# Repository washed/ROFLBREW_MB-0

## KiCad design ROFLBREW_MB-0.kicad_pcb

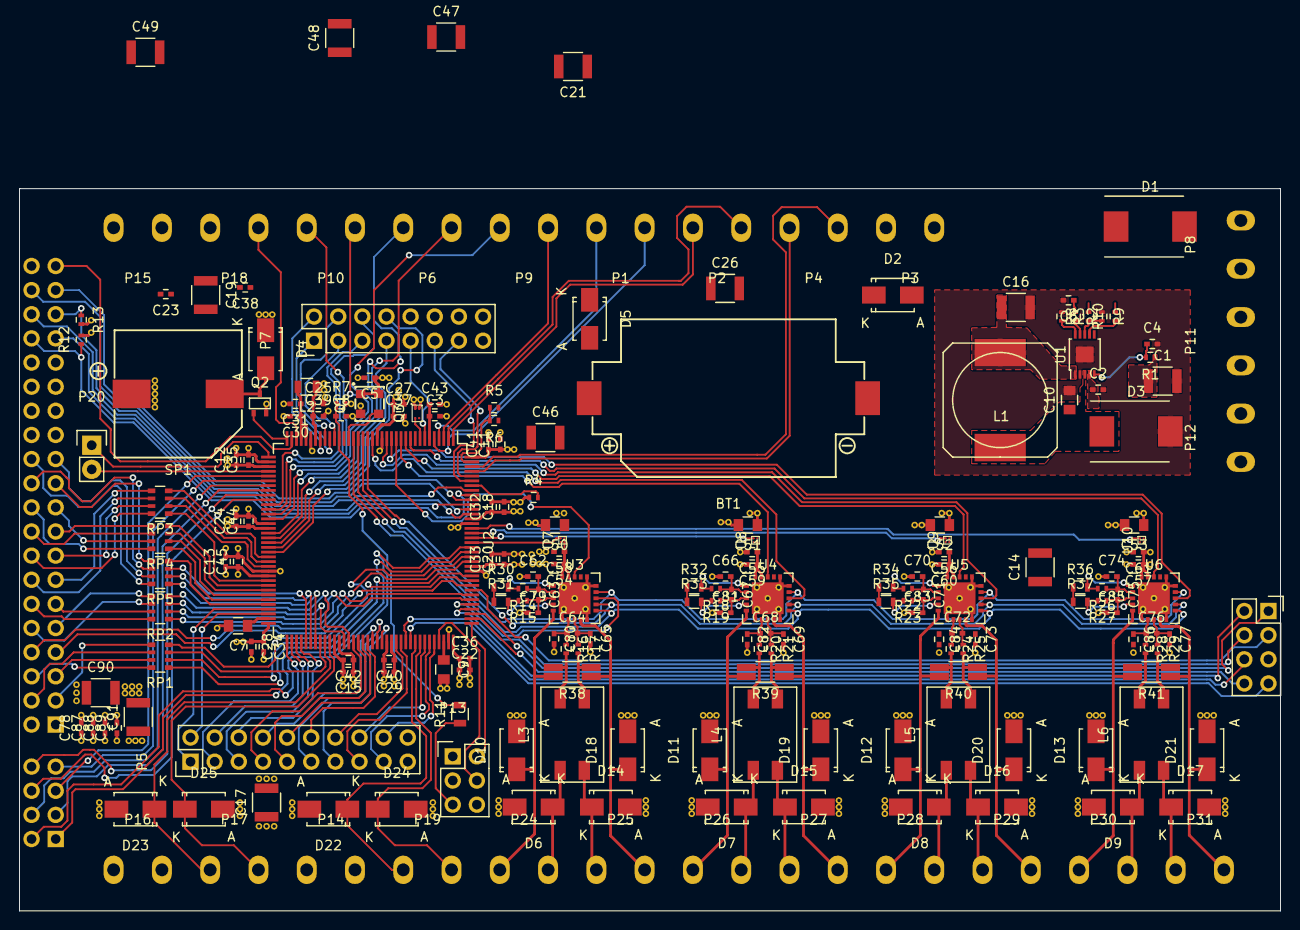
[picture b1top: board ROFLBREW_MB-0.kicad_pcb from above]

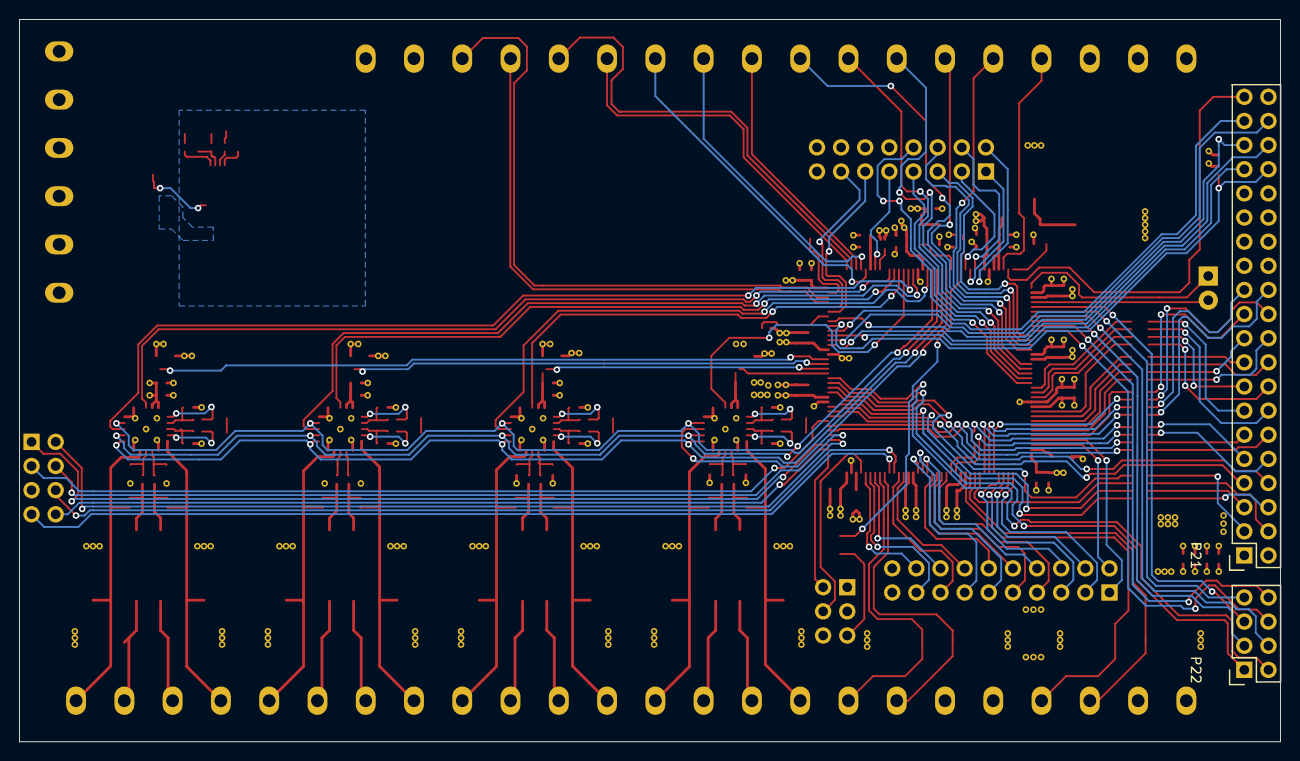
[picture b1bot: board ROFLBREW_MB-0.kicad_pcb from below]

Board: 4 copper layers, 132.7 x 76.0 mm, 214 parts (2 on the bottom side), 202 nets.

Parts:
BT1: Battery; MPDBA2032SM
C1, C14, C16, C17, C19, C21, C26, C46, C47, C48, C49, C90, C91: 22µ; C_1210
C2, C3, C4, C5, C6, C8, C11, C12, C13, C15, C18, C20, C22, C23, C24, C25, C27, C28, C29, C31, C43, C54, C55, C56, C57, C58, C59, C60, C61, C88, C89: 100n; C_0402
C7, C9: 2µ2; C_0805
C10: 470n; C_0805
C30, C32, C33, C34, C35, C36, C37, C38, C39, C40, C41, C42, C44, C45, C63, C64, C67, C68, C71, C72, C75, C76, C78, C87: 10n; C_0402
C50, C51, C52, C53: 1µ; C_0805
C62, C65, C66, C69, C70, C73, C74, C77, C79, C80, C81, C82, C83, C84, C85, C86: 1n; C_0402
D1, D3: MBRS340; DO-214AB
D2, D4, D5: B240; SMA_Standard
D6, D7, D8, D9, D10, D11, D12, D13, D14, D15, D16, D17, D18, D19, D20, D21, D22, D23, D24, D25: TVS; SMA_Standard
L1: 4µ7; SELF-WE-PD-XXL
L2: Ferrite Bead; R_0805
L3, L4, L5, L6: WE-SL2
P1, P2, P3, P4, P6, P8, P9, P10, P11, P12, P14, P15, P16, P17, P18, P19, P24, P25, P26, P27, P28, P29, P30, P31: CONN_01X02; PM_5.08_2
P5: CONN_02X10; Pin_Header_Straight_2x10
P7: CONN_02X08; Pin_Header_Straight_2x08
P13: CONN_02X03; Pin_Header_Straight_2x03
P20: CONN_01X02; Pin_Header_Straight_1x02
P21: CONN_02X20; Socket_Strip_Straight_2x20
P22, P23: CONN_02X04; Socket_Strip_Straight_2x04
Q1: ASEM1
Q2: MUN5233T1G; SC-70
Q3: ASTMTXK
R1, R9, R10: 100K; R_0402
R2: 14K; R_0402
R3: 40K2; R_0402
R4, R5, R6, R7: 10K; R_0402
R8: 316K; R_0402
R11: 0R; R_0805
R12, R13: 4K7 DNI; R_0402
R14, R15, R16, R17, R18, R19, R20, R21, R22, R23, R24, R25, R26, R27, R28, R29: TBD R; R_0402
R30, R31, R32, R33, R34, R35, R36, R37: 2k 0.01%; R_0603
R38, R39, R40, R41: 1k RTD PT1000 DNI; R_1206_RTD_SPLITPADS
RP1, RP2, RP3, RP4, RP5: R_PACK4; R_Array_Convex_4x0603
SP1: SPEAKER; CT-1205H
U1: LT3480; MSOP-10-1EP_3x3mm_Pitch0.5mm
U2: STM32F756ZGTx; LQFP-144_20x20mm_Pitch0.5mm
U3, U4, U5, U6: MAX31865; QFN-20-1EP_5x5mm_Pitch0.65mm
U7, U8, U9, U10: TPS2290x; TPS229x

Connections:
+3V3: C5.1, C11.1, C12.1, C13.1, C14.1, C15.1, C16.1, C17.1, C18.1, C19.1, C20.1, C21.1, C22.1, C23.1, C24.1, C25.1, C27.1, C28.1, C29.1, C32.1, C33.1, C34.1, C35.1, C36.1, C37.1, C38.1, C39.1, C40.1, C41.1, C42.1, C44.1, C45.1, C46.1, C47.1, C48.1, C49.1, C50.1, C51.1, C52.1, C53.1, C78.1, C87.1, C88.1, C89.1, C90.1, C91.1, D4.1, L1.2, L2.1, P3.1, P12.2, P13.1, P14.1, P15.1, P16.1, P21.2, Q1.1, Q1.4, R5.2, R7.2, R8.2, R10.2, R12.2, R13.2, SP1.1, U1.1, U2.17, U2.30, U2.39, U2.52, U2.62, U2.72, U2.84, U2.95, U2.108, U2.121, U2.131, U2.144, U7.A1, U8.A1, U9.A1, U10.A1
+12V: C1.1, C2.1, D1.1, R1.1, U1.4
+BATT: C3.1, C26.1, C43.1, D2.1, D5.1, Q3.3, U2.6
/ADC1_IN0: P18.1, U2.34
/ADC1_IN4: P20.2, U2.40
/ADC1_IN9: P7.5, U2.47
/ADC1_IN10: P7.3, U2.26
/ADC1_IN11: P7.1, U2.27
/ADC1_IN12: P7.4, U2.28
/ADC1_IN13: P7.2, U2.29
/FLASH_CS: P22.8, U2.45
/FLASH_WP: P22.6, U2.46
/FONT/FLASH_MISO: P22.7, U2.42
/FONT/FLASH_MOSI: P22.4, U2.43
/FONT/FLASH_SCK: P22.5, U2.41
/FONT_CS: P22.3, U2.44
/LCD_BLT: P21.39, U2.35
/LCD_CS: P21.3, RP1.5
/LCD_CS_MCU: RP1.4, U2.123
/LCD_D0: P21.9, RP2.5
/LCD_D0_MCU: RP2.3, U2.85
/LCD_D1: P21.10, RP2.6
/LCD_D1_MCU: RP2.4, U2.86
/LCD_D2: P21.11, RP2.7
/LCD_D2_MCU: RP2.2, U2.114
/LCD_D3: P21.12, RP2.8
/LCD_D3_MCU: RP2.1, U2.115
/LCD_D4: P21.13, RP3.5
/LCD_D4_MCU: RP3.4, U2.58
/LCD_D5: P21.14, RP3.6
/LCD_D5_MCU: RP3.3, U2.59
/LCD_D6: P21.15, RP3.7
/LCD_D6_MCU: RP3.2, U2.60
/LCD_D7: P21.16, RP3.8
/LCD_D7_MCU: RP3.1, U2.63
/LCD_D8: P21.17, RP4.5
/LCD_D8_MCU: RP4.4, U2.64
/LCD_D9: P21.18, RP4.6
/LCD_D9_MCU: RP4.3, U2.65
/LCD_D10: P21.19, RP4.7
/LCD_D10_MCU: RP4.2, U2.66
/LCD_D11: P21.20, RP4.8
/LCD_D11_MCU: RP4.1, U2.67
/LCD_D12: P21.21, RP5.5
/LCD_D12_MCU: RP5.4, U2.68
/LCD_D13: P21.22, RP5.6
/LCD_D13_MCU: RP5.3, U2.77
/LCD_D14: P21.23, RP5.7
/LCD_D14_MCU: RP5.2, U2.78
/LCD_D15: P21.24, RP5.8
/LCD_D15_MCU: RP5.1, U2.79
/LCD_DATA/CMD: P21.4, RP1.6
/LCD_DATA/CMD_MCU: RP1.3, U2.80
/LCD_GPIO1: P22.1, U2.124
/LCD_GPIO2: P22.2, U2.125
/LCD_RD#: P21.5, RP1.7
/LCD_RD#_MCU: RP1.2, U2.118
/LCD_TE: P21.8, U2.122
/LCD_WR#: P21.6, RP1.8
/LCD_WR#_MCU: RP1.1, U2.119
/LCD_nRST: P21.7, U2.117
/PA10: P5.16, U2.102
/PA11: P5.17, U2.103
/PA12: P5.18, U2.104
/PB2: P7.6, U2.48
/PB8: P7.11, U2.139
/PB9: P7.13, U2.140
/PB10: P5.1, U2.69
/PB11: P5.2, U2.70
/PB12: P5.3, U2.73
/PB13: P5.4, U2.74
/PB14: P5.5, U2.75
/PB15: P5.6, U2.76
/PC13: P7.9, U2.7
/PG0: P7.7, U2.56
/PG1: P7.8, U2.57
/PG2: P5.7, U2.87
/PG3: P5.9, U2.88
/PG4: P5.10, U2.89
/PG5: P5.12, U2.90
/PG6: P5.8, U2.91
/PG7: P5.11, U2.92
/PG8: P5.13, U2.93
/PWM_1: Q2.1, U2.36
/PWM_2: P20.1, U2.37
/ROTENC0_A: D22.1, P19.1, U2.100
/ROTENC0_B: D24.1, P19.2, U2.101
/ROTENC1_A: D23.1, P17.1, U2.81
/ROTENC1_B: D25.1, P17.2, U2.82
/RTC_OSC: Q3.2, U2.8
/RTD0_CS: U2.22, U3.13
/RTD0_DRDY: U2.13, U3.18
/RTD1_CS: U2.18, U4.13
/RTD1_DRDY: U2.12, U4.18
/RTD2_CS: U2.15, U5.13
/RTD2_DRDY: U2.11, U5.18
/RTD3_CS: U2.14, U6.13
/RTD3_DRDY: U2.10, U6.18
/RTD_MISO: U2.20, U3.14, U4.14, U5.14, U6.14
/RTD_MOSI: U2.21, U3.11, U4.11, U5.11, U6.11
/RTD_PWR_0: U2.126, U7.B1
/RTD_PWR_1: U2.127, U8.B1
/RTD_PWR_2: U2.128, U9.B1
/RTD_PWR_3: U2.129, U10.B1
/RTD_SCK: U2.19, U3.12, U4.12, U5.12, U6.12
/SD_CARDD: P23.8, U2.110
/SD_CLK: P23.4, U2.113
/SD_CMD: P23.3, U2.116
/SD_D0: P23.6, U2.98
/SD_D1: P23.7, U2.99
/SD_D2: P23.1, U2.111
/SD_D3: P23.2, U2.112
/SPI4_CS0: P2.1, U2.2
/SPI4_CS1: P9.1, U2.3
/SPI4_MISO: P1.2, U2.4
/SPI4_MOSI: P1.1, U2.5
/SPI4_SCK: P2.2, U2.1
/SYS_JTCK: P13.2, U2.109
/SYS_JTMS: P13.4, U2.105
/TIM3_CH1: P5.14, U2.96
/TIM3_CH2: P5.15, U2.97
/TP_INT: P21.36, U2.132
/TP_PEN: P21.38, U2.133
/TP_SCL: P21.34, R12.1, U2.136
/TP_SDA: P21.35, R13.1, U2.137
/TP_WAKE: P21.37, U2.135
/TP_nRST: P21.33, U2.134
/UART8_RX: P4.2, U2.141
/UART8_TX: P4.1, U2.142
/nRST: C8.1, R7.1, R11.2, U2.25
GND: BT1.2, C1.2, C2.2, C3.2, C4.2, C5.2, C6.2, C7.2, C8.2, C9.2, C10.2, C11.2, C12.2, C13.2, C14.2, C15.2, C16.2, C17.2, C18.2, C19.2, C20.2, C21.2, C22.2, C23.2, C24.2, C25.2, C26.2, C27.2, C28.2, C29.2, C30.2, C31.2, C32.2, C33.2, C34.2, C35.2, C36.2, C37.2, C38.2, C39.2, C40.2, C41.2, C42.2, C43.2, C44.2, C45.2, C46.2, C47.2, C48.2, C49.2, C50.2, C51.2, C52.2, C53.2, C54.2, C55.2, C56.2, C57.2, C58.2, C59.2, C60.2, C61.2, C62.1, C65.2, C66.1, C69.2, C70.1, C73.2, C74.1, C77.2, C78.2, C79.1, C80.2, C81.1, C82.2, C83.1, C84.2, C85.1, C86.2, C87.2, C88.2, C89.2, C90.2, C91.2, D3.2, D6.2, D7.2, D8.2, D9.2, D10.2, D11.2, D12.2, D13.2, D14.2, D15.2, D16.2, D17.2, D18.2, D19.2, D20.2, D21.2, D22.2, D23.2, D24.2, D25.2, P3.2, P8.1, P11.1, P12.1, P13.3, P14.2, P15.2, P16.2, P21.1, P21.40, P23.5, Q1.2, Q2.2, Q3.1, Q3.4, R3.1, R4.1, R6.1, R9.1, U1.2, U1.11, U2.16, U2.31, U2.38, U2.51, U2.61, U2.83, U2.94, U2.107, U2.120, U2.130, U3.6, U3.10, U3.15, U3.16, U3.21, U4.6, U4.10, U4.15, U4.16, U4.21, U5.6, U5.10, U5.15, U5.16, U5.21, U6.6, U6.10, U6.15, U6.16, U6.21, U7.B2, U8.B2, U9.B2, U10.B2
unnamed: BT1.1, D5.2
unnamed: C4.1, R1.2, U1.5
unnamed: C6.1, R2.1
unnamed: C7.1, U2.71
unnamed: C9.1, U2.106
unnamed: C10.1, D3.1, L1.1, U1.3
unnamed: C54.1, C58.1, U3.19, U3.20, U7.A2
unnamed: C55.1, C59.1, U4.19, U4.20, U8.A2
unnamed: C56.1, C60.1, U5.19, U5.20, U9.A2
unnamed: C57.1, C61.1, U6.19, U6.20, U10.A2
unnamed: C62.2, C63.1, R14.1, U3.2
unnamed: C63.2, C79.2, R15.1, U3.3
unnamed: C64.1, C80.1, R16.1, U3.7
unnamed: C64.2, C65.1, R17.1, U3.8
unnamed: C66.2, C67.1, R18.1, U4.2
unnamed: C67.2, C81.2, R19.1, U4.3
unnamed: C68.1, C82.1, R20.1, U4.7
unnamed: C68.2, C69.1, R21.1, U4.8
unnamed: C70.2, C71.1, R22.1, U5.2
unnamed: C71.2, C83.2, R23.1, U5.3
unnamed: C72.1, C84.1, R24.1, U5.7
unnamed: C72.2, C73.1, R25.1, U5.8
unnamed: C74.2, C75.1, R26.1, U6.2
unnamed: C75.2, C85.2, R27.1, U6.3
unnamed: C76.1, C86.1, R28.1, U6.7
unnamed: C76.2, C77.1, R29.1, U6.8
unnamed: D1.2, P8.2
unnamed: D2.2, P11.2
unnamed: D4.2, Q2.3, SP1.2
unnamed: D6.1, L3.3, P24.2
unnamed: D7.1, L4.3, P26.2
unnamed: D8.1, L5.3, P28.2
unnamed: D9.1, L6.3, P30.2
unnamed: D10.1, L3.2, P24.1, R16.2, R38.2, U3.5
unnamed: D11.1, L4.2, P26.1, R20.2, R39.2, U4.5
unnamed: D12.1, L5.2, P28.1, R24.2, R40.2, U5.5
unnamed: D13.1, L6.2, P30.1, R28.2, R41.2, U6.5
unnamed: D14.1, L3.4, P25.1
unnamed: D15.1, L4.4, P27.1
unnamed: D16.1, L5.4, P29.1
unnamed: D17.1, L6.4, P31.1
unnamed: D18.1, L3.1, P25.2, R17.2, R38.1, U3.9
unnamed: D19.1, L4.1, P27.2, R21.2, R39.1, U4.9
unnamed: D20.1, L5.1, P29.2, R25.2, R40.1, U5.9
unnamed: D21.1, L6.1, P31.2, R29.2, R41.1, U6.9
unnamed: P6.1, U2.55
unnamed: P6.2, U2.54
unnamed: P9.2, U2.53
unnamed: P10.1, U2.50
unnamed: P10.2, U2.49
unnamed: P13.5, R11.1
unnamed: Q1.3, U2.23
unnamed: R2.2, U1.9
unnamed: R3.2, U1.10
unnamed: R4.2, U2.138
unnamed: R5.1, R6.2, U2.143
unnamed: R8.1, R9.2, U1.8
unnamed: R10.1, U1.7
unnamed: R14.2, R30.2, U3.1
unnamed: R15.2, R31.2, U3.4
unnamed: R18.2, R32.2, U4.1
unnamed: R19.2, R33.2, U4.4
unnamed: R22.2, R34.2, U5.1
unnamed: R23.2, R35.2, U5.4
unnamed: R26.2, R36.2, U6.1
unnamed: R27.2, R37.2, U6.4
unnamed: R30.1, R31.1
unnamed: R32.1, R33.1
unnamed: R34.1, R35.1
unnamed: R36.1, R37.1
VDDA: C30.1, C31.1, L2.2, U2.32, U2.33

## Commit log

2017-03-01 Add .gitignore
2017-03-11 Something changed :)
2017-03-11 Add power_switches library
2017-03-11 Add power switches to MAX31865 supply pins
2017-03-11 Update netlist with power switch footprints
2017-03-12 Update some component footprints, add SD card and RTD power routing
